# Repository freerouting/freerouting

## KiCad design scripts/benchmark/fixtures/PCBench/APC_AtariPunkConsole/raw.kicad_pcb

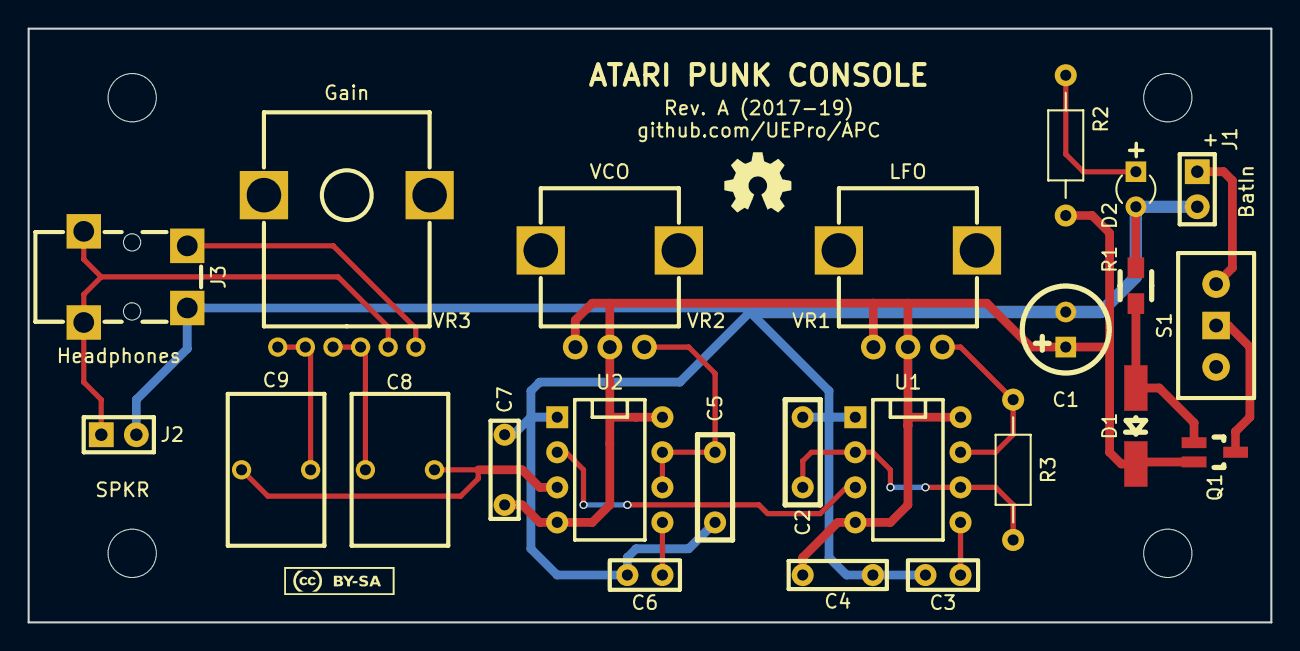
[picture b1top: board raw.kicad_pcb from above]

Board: 2 copper layers, 90.0 x 43.0 mm, 30 parts (0 on the bottom side), 17 nets.

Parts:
C1: 220µ/16V; C_round-radial-polar-2,5mm-6,3mm
C2: 10n; C_rect-radial-bipolar-200mil-2,5x7mm
C3, C6: 10n; C_rect-radial-bipolar-100mil-2x5mm
C4, C7: 100n; C_rect-radial-bipolar-200mil-2x7,5mm
C5: 100n; C_rect-radial-bipolar-200mil-2,5x7mm
C8, C9: 2µ2; C-Rect_L7_W11_P5
D1: 4V7; Diode_MiniMELF-Handsoldering
D2: 3mm/cyan; LED_2pin-3mm
Des*: Val*; MountingHole-3,5mm
Des*#2, Des*#3, Des*#4: Val*; MountingHole-3,5mm
J1: BatIn; PinArray-100mil-1x2
J2: Speaker; PinArray-100mil-1x2
J3: Klinke-stereo; Lumberg-1503-07-Klinke-3,5mm
Q1: FDN304; SOT23-Handsoldering
R1: 10k; SMD0805-HandSoldering
R2: 10k; R_axial_400mil
R3: 1k; R_axial_400mil
S1: S_1P2T; S-Schiebeschalter_China_SPDT
U1, U2: NE555; DIP-8_300
VAL: REF; CC-BY-SA_08mm_Fsi
VAL#2: REF; oshw5mm
VR1, VR2: 500k; VR-vert_PCB_china
VR3: 10k log; VR-Alps_R12L_vert

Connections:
+9V: C1.1, C4.1, C7.1, D1.2, Q1.2, R2.1, U1.4, U1.8, U2.4, U2.8, VR1.1, VR1.2, VR2.1, VR2.2
GND: C1.2, C2.2, C3.2, C4.2, C5.2, C6.2, C7.2, D2.2, J1.2, J2.2, J3.1, R1.2, U1.1, U2.1
unnamed: C2.1, R3.1, U1.2, U1.6
unnamed: C3.1, U1.5
unnamed: C5.1, U2.6, U2.7, VR2.3
unnamed: C6.1, U2.5
unnamed: C8.1, C9.1, U2.3
unnamed: C8.2, VR3.1, VR3.2
unnamed: C9.2, VR3.4, VR3.5
unnamed: D1.1, Q1.1, R1.1
unnamed: D2.1, R2.2
unnamed: J1.1, S1.3
unnamed: J2.1, J3.3, VR3.3
unnamed: J3.2, VR3.6
unnamed: Q1.3, S1.2
unnamed: R3.2, U1.7, VR1.3
unnamed: U1.3, U2.2

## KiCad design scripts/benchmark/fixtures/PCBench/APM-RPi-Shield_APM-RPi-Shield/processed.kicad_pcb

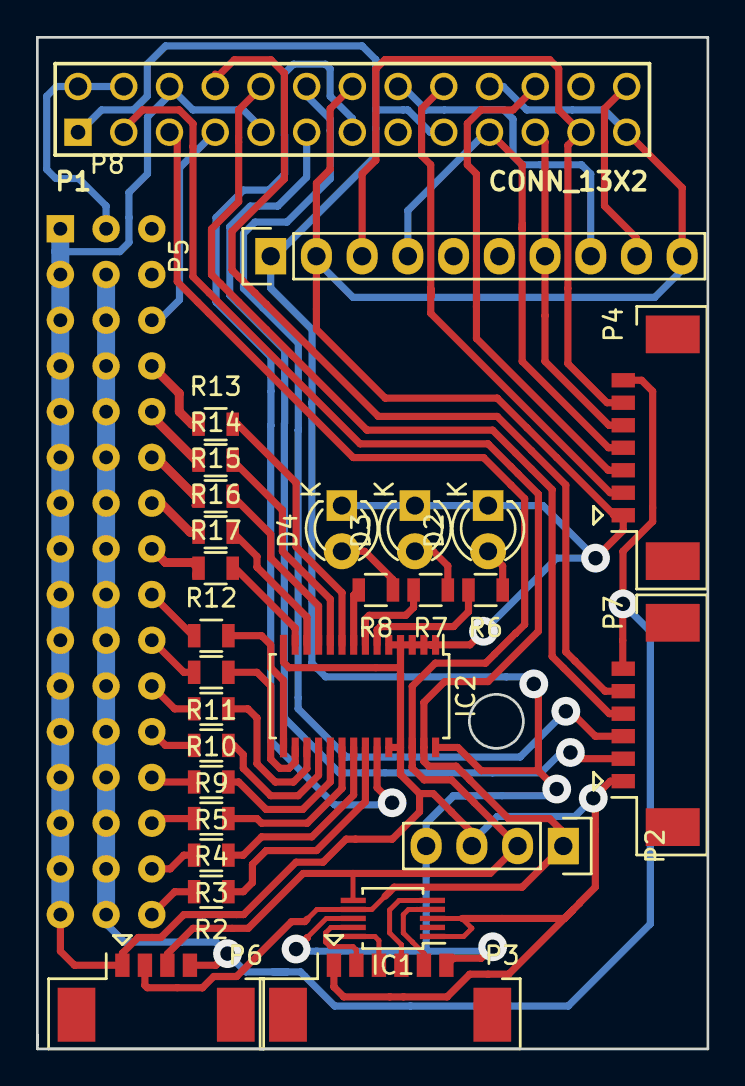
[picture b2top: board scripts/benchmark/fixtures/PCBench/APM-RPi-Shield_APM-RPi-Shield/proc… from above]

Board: 2 copper layers, 37.2 x 56.2 mm, 29 parts (0 on the bottom side), 55 nets.

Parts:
D2: YELLOW; LED-3MM
D3: RED; LED-3MM
D4: BLUE; LED-3MM
IC1: ADS1115; MSOP-10_3x3mm_Pitch0.5mm
IC2: PCA9685; TSSOP-28_4.4x9.7mm_Pitch0.65mm
P1: CONN_13X2; pin_array_13x2
P2: BMP180; Pin_Header_Straight_1x04
P3: ADC; Connector_Molex_PicoBlade_53398-0671
P4: SPI; Connector_Molex_PicoBlade_53398-0771
P5: MPU9250; Pin_Header_Straight_1x10
P6: I2C; Connector_Molex_PicoBlade_53398-0471
P7: UART; Connector_Molex_PicoBlade_53398-0671
P8: CONN_03X16; Pin_Header_Straight_3x16
R2, R3, R4, R5, R6, R7, R8, R9, R10, R11, R12, R13, R14, R15, R16, R17: 200; R_0805

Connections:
+3V3: IC1.8, IC2.28, P1.1, P1.17, P2.4, P3.6, P5.1
+5V: P1.2, P1.4, P8.17
/BEC_5V: P4.7, P6.4, P7.6, P8.18, P8.19, P8.20, P8.21, P8.22, P8.23, P8.24, P8.25, P8.26, P8.27, P8.28, P8.29, P8.30, P8.31, P8.32
/GPIO0(SDA): IC1.7, IC2.27, P1.3, P2.1, P6.2
/GPIO1(SCL): IC1.6, IC2.26, P1.5, P2.2, P6.3
/GPIO4(PPM): P1.7, P8.35
/GPIO7(CE1): P1.26, P5.9
/GPIO9(MISO): P1.21, P4.5, P5.7
/GPIO10(MOSI): P1.19, P4.4, P5.4
/GPIO11(SCLK): P1.23, P4.6, P5.3
/GPIO17: P1.11, P7.2
/GPIO18: P1.12, P7.3
/GPIO23: P1.16, P5.8
/GPIO24: P1.18, P4.2
/GPIO25: P1.22, P4.3
/GPIO27: IC2.23, P1.13
/RXD: P1.10, P7.4
/SERVO_S1: P8.36, R13.1
/SERVO_S2: P8.37, R14.1
/SERVO_S3: P8.38, R15.1
/SERVO_S4: P8.39, R16.1
/SERVO_S5: P8.40, R17.1
/SERVO_S6: P8.41, R12.1
/SERVO_S7: P8.42, R11.2
/SERVO_S8: P8.43, R10.2
/SERVO_S9: P8.44, R9.2
/SERVO_S10: P8.45, R5.2
/SERVO_S11: P8.46, R4.2
/SERVO_S12: P8.47, R3.2
/SERVO_S13: P8.48, R2.2
/TXD: P1.8, P7.5
GND: D2.1, D3.1, D4.1, IC1.1, IC1.3, IC2.1, IC2.2, IC2.3, IC2.4, IC2.5, IC2.14, IC2.24, IC2.25, P1.6, P1.9, P1.14, P1.20, P1.25, P2.3, P3.1, P4.1, P5.2, P5.10, P6.1, P7.1, P8.1, P8.2, P8.3, P8.4, P8.5, P8.6, P8.7, P8.8, P8.9, P8.10, P8.11, P8.12, P8.13, P8.14, P8.15, P8.16
unnamed: D2.2, R6.1
unnamed: D3.2, R7.1
unnamed: D4.2, R8.1
unnamed: IC1.4, P3.5
unnamed: IC1.5, P3.4
unnamed: IC1.9, P3.2
unnamed: IC1.10, P3.3
unnamed: IC2.6, R6.2
unnamed: IC2.7, R7.2
unnamed: IC2.8, R8.2
unnamed: IC2.9, R13.2
unnamed: IC2.10, R14.2
unnamed: IC2.11, R15.2
unnamed: IC2.12, R16.2
unnamed: IC2.13, R17.2
unnamed: IC2.15, R12.2
unnamed: IC2.16, R11.1
unnamed: IC2.17, R10.1
unnamed: IC2.18, R9.1
unnamed: IC2.19, R5.1
unnamed: IC2.20, R4.1
unnamed: IC2.21, R3.1
unnamed: IC2.22, R2.1

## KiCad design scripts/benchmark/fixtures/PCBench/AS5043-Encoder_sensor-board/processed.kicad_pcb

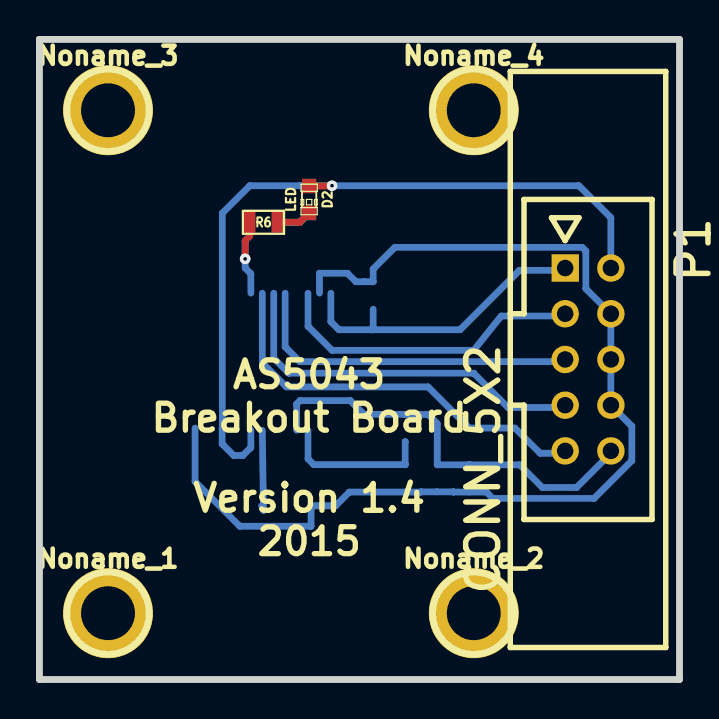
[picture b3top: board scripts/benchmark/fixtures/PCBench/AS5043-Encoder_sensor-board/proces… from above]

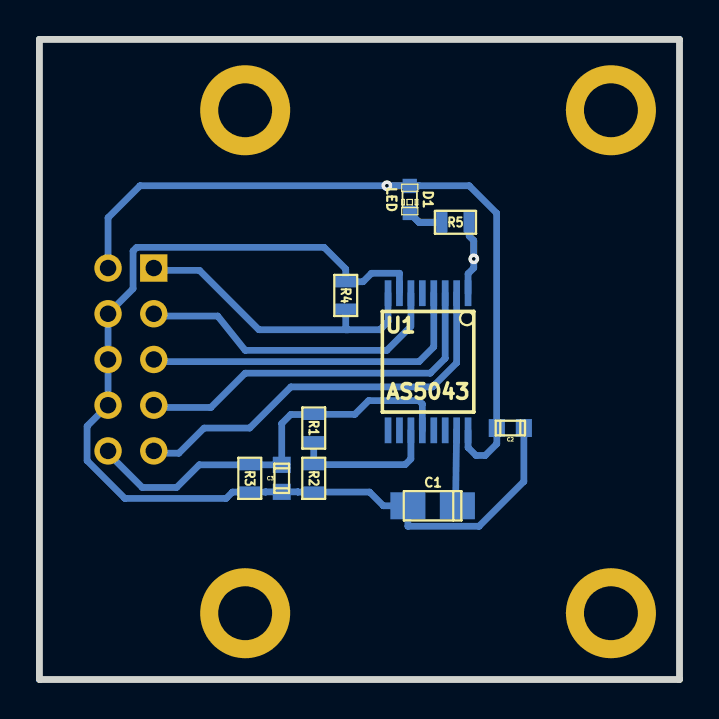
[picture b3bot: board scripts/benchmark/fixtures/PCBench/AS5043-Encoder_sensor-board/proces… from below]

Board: 2 copper layers, 35.6 x 35.6 mm, 17 parts (10 on the bottom side), 13 nets.

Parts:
C1: 5uF; c_tant_A
C2: 100nF; c_0603
C3: 100pf; c_0603
D1, D2: LED; LED-0603
Noname_1, Noname_2, Noname_3, Noname_4: P***; 1pin
P1: CONN_5X2; he10-lock
R1, R2: 33k; SM0603
R3: 47k; SM0603
R4: 10k; SM0603
R5, R6: 1k; SM0603
U1: AS5043; SSOP16_WIDE

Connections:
+5V: C2.1, D1.1, D2.1, P1.2, U1.16
/CLK: P1.5, U1.4
/CS: P1.7, U1.3
/DO: P1.3, U1.6
/MODE: P1.9, U1.2
/PROG: P1.1, R4.1, U1.8
GND: C1.2, C2.2, C3.2, P1.4, P1.6, P1.8, R2.2, R3.2, R4.2, U1.7
unnamed: C1.1, U1.15
unnamed: C3.1, P1.10, R1.1, R3.1, U1.12
unnamed: D1.2, R5.1
unnamed: D2.2, R6.1
unnamed: R1.2, R2.1, U1.11
unnamed: R5.2, R6.2, U1.1
